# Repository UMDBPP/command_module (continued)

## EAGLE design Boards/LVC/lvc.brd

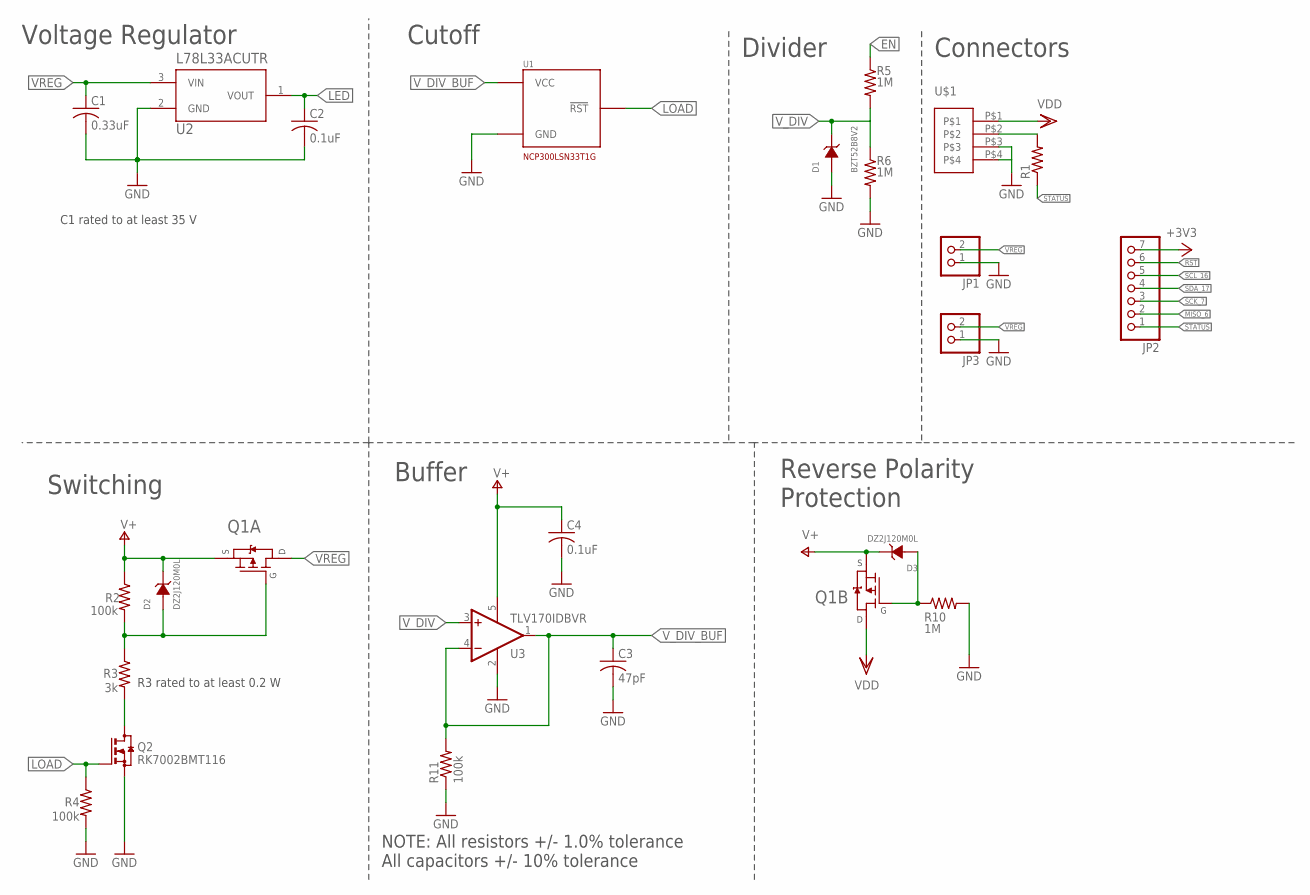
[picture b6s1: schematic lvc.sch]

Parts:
C1: 0.33uF; C0603
C2, C4: 0.1uF; C0603
C3: 47pF; C0603
D1: BZT52B8V2; SOD123
D2, D3: DZ2J120M0L; SMINI2-F5-B
JP1, JP3: PINHD-1X2; 1X02
JP2: PINHD-1X7; 1X07
Q1: SI7997DP; POWERPAK-SO-8-DUAL
Q2: RK7002BMT116; SOT23
R1: R-US_R0603; R0603
R2, R4, R11: 100k; R0603
R3: 3k; R0603
R5, R6, R10: 1M; R0603
U1: NCP300LSN33T1G; SOT23-5
U2: L78L33ACUTR; SOT-89
U3: TLV170IDBVR; SOT23-DBV
U$1: MICROCLASP_4; 4_PIN_MICROCLASP

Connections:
EN: R5.1
GND: C1.2, C2.2, C3.2, C4.2, D1.A, JP1.1, JP3.1, Q2.2 (S), R4.2, R6.2, R10.2, R11.1, U1.3 (GND), U2.2 (GND), U3.2 (V-), U$1.P$3, U$1.P$4
LED: C2.1, U2.1 (VOUT)
LOAD: Q2.1 (G), R4.1, U1.1 (!RST!)
MISO_6: JP2.2
unnamed: R1.2, U$1.P$2
unnamed: D2.A, Q1.4 (G), R2.2, R3.1
unnamed: D3.A, Q1.2 (G), R10.1
unnamed: Q2.3 (D), R3.2
RST: JP2.6
SCK_7: JP2.3
SCL_16: JP2.5
SDA_17: JP2.4
STATUS: JP2.1, R1.1
V+: C4.1, D2.C, D3.C, Q1.1 (S), Q1.3 (S), R2.1, U3.5 (V+)
VDD: Q1.7 (D), Q1.8 (D), Q1.8L (D), U$1.P$1
VREG: C1.1, JP1.2, JP3.2, Q1.5 (D), Q1.5L (D), Q1.6 (D), U2.3 (VIN)
V_DIV: D1.C, R5.2, R6.1, U3.3 (+IN)
V_DIV_BUF: C3.1, R11.2, U1.2 (VCC), U3.1 (OUT), U3.4 (-IN)

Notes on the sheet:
Voltage Regulator
Switching
Divider
Connectors
Reverse Polarity Protection
Cutoff
NOTE: All resistors +/- 1.0% tolerance All capacitors +/- 10% tolerance
C1 rated to at least 35 V
R3 rated to at least 0.2 W
Buffer

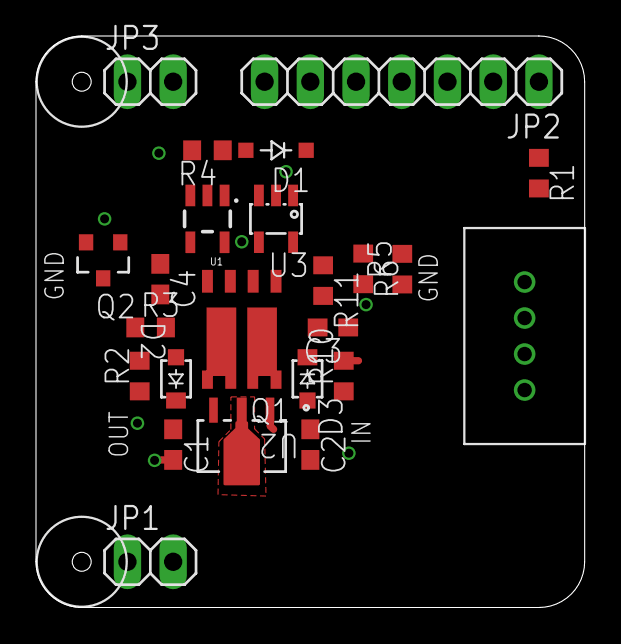
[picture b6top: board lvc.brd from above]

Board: 2 copper layers, 30.5 x 31.8 mm, 24 parts (0 on the bottom side), 13 nets.

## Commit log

2020-01-08 Initial commit with boards
2020-01-09 Routed cell tracker board with power reg
2020-01-18 Cell tracker V3 routed
2020-01-19 Cleaned up the BITS schematic
2020-01-19 cleaned up cell schematic
2020-01-20 Removing 3v3 line, fixing the MOSFET I broke
2020-01-20 Cell Mosfet swap
2020-01-20 General board parts placement for BITS
2020-01-21 Dump of CAD files
2020-01-21 reverted bits schematic back to my last commit"
2020-01-21 Revert "reverted bits schematic back to my last commit""
    This reverts commit d8380e26c9c134d67ee78542be9b2ca2b8e420f0.
2020-01-21 Better fidelity cad
2020-01-21 Add cmdLibs lib
2020-01-21 Maybe fixing supply 1
2020-01-21 v7 Compatible file upload
2020-01-21 Integrate the BITS XBee
2020-01-21 Pushing the compatible version
2020-01-21 Updated the inductor and mosfet in cell schematic
2020-01-21 Adding connector to lib
2020-01-22 routed bits board
2020-01-22 Created an alternate board
2020-01-22 bits board try 2
2020-01-23 put connector on cell board, plus lots of cad work
2020-01-24 a whole lot of finshed nonsense
2020-02-04 All of the changes with CAD and electronics since switching to the microclasp connectors
2020-02-05 fixes and design review slides
2020-02-16 Updated boards
2020-05-13 Reorganizing files for new boards
2020-05-13 Fixing Errors, ditching coincell
2020-05-16 Fixing BITS brd
2020-05-19 Bunches of CAD, but I don't like CAD
2020-05-29 Box Passthroughs, fixing Iridium Board
2020-06-15 not much
2020-06-15 Adding Gitignore for s#h and b#d
2020-06-15 Changing antenna conf
2020-06-15 Putting all the code into this repo
2020-06-15 modding GS for choppy
2020-06-19 updating resistors for correct cutoff
2020-06-26 Code+nearly completed boards
2020-07-03 Moved libs, adding isolator
2020-07-04 More stuff, close, not done
2020-07-05 Finishing touches for Cell3.2
2020-07-06 Finalizing BITS v3.2
2020-07-12 Final board export/cam, code libraries fld
2020-07-13 Handling R values
2020-07-14 minor R val changes, STEP generation
2020-07-26 API testing/cellv3.1trigger software failREP
2020-07-26 Added board step files to CAD fld
2020-07-27 more liteAPRS debugging
2020-07-29 BITS3v1 flight code, liteAPRS code
2020-08-01 CellCode
2020-08-02 jtXBee updates
2020-08-02 Include active jtXBee files
2020-08-03 celltracker sms_rx done, memredux
2020-08-07 NS92 prelim code FRZ
2020-08-17 Cell Assem Fin
2020-08-20 Cell Board appears to work
2020-08-26 New GPS procedures
2020-08-29 NewCell fixes
2020-08-30 Cell3.2 working, freeze
2020-08-30 NS93_code_FRZ
2020-09-03 Debugging Cell3v2
2020-09-15 buffer simplification
2020-10-09 New Testing File, v3.2 test
2020-10-16 New folder for test code, with in house gps lib
2020-10-16 setting up gps lib test
2021-01-09 Trying some new hardware configs
2021-01-11 changing some colors and taking screenshots
2021-01-15 a commit
2021-01-20 plate mounting bolt holes
2021-01-25 Adding a copy of the AdafruitRFM95 board for ref
2021-01-25 LightAPRS switching reg/LVC updates
2021-01-25 routed lightAPRS LVC
2021-01-26 Finished new LightAPRS LVC/REG
2021-02-01 Cutting down the adafruit rfm board
2021-02-20 box fixes
2021-03-14 Box changes
2021-03-15 New_lid
2021-03-18 Adding in Bitsv2 board CAD
2021-03-18 re-order/confirm LVC fix
2021-03-31 Plate mounting holes
2021-04-03 new_reg work
    LMR50410XF reg design to cover and possibly replace LMR16020 for <1A command things
2021-07-06 plate for v2 bits brd
2021-07-08 lightAPRS code fix
2021-08-08 re-arrange some file structure, init boxv4
2021-08-08 Box v4 draft
2021-08-19 New reg board
    LM20242
2021-09-16 routed board...?
2021-09-26 improved spacing between rockblock and bits board on plate
2021-10-03 BITSv4
    omg I need a clock so bad
2021-10-04 LED reposition
2021-10-09 connector move
2021-10-13 TextMove
2021-12-11 new choppy
2022-01-02 code for second xbee trigger using arduino pro mini
2022-01-12 file changes
2022-04-16 TestedBoard
    omg_it_works
2022-04-17 BoardUpdate
2022-04-19 Clone v3.2 to v4
2022-04-19 Comments, lots of Comments
2022-04-21 Completed Commenting Primary File
2022-04-21 Enough changes a test should happen
2022-04-21 Added voltage reporting
2022-04-22 Unbroke the code again
2022-04-22 AvgAscentRate added
2022-04-25 FixingErrors
    snprintf unhappy, modifying that
2022-04-25 Another Fix
2023-05-26 new ghoul xbee
2023-07-31 bits v5 board begins
2023-07-31 BITSv5 updates
2023-08-11 BITSv5 sch almost done
2023-08-13 more bits updates
2023-08-18 bits v5 board nearly done
2023-08-19 several hundred bits v5 errors later
2023-08-20 bits v5 board feedback added
2023-08-20 no more 5 am commits
2023-08-23 BITSv5 layout changes
2023-08-25 small update to BITSv5 for review
2023-08-26 BITSv5 board done
2023-08-26 xbee joint board begins
2023-08-28 xbee joint board updates
2023-08-30 xbee joint and bits updates
2023-09-04 most up to date bits and xbee joint
2023-09-04 added button to BITS5
2023-09-04 working on xbee joint
2023-09-05 xbee joint layout almost complete
2023-09-05 BITSv5 USB change
2023-09-05 BITSv5 added additional Xbee connector
2023-10-09 ns122 updates to do
2023-10-19 bits v5 w/ dorji radio
2023-10-19 dorji joint?
2023-10-23 ordered new joint and bits
2023-11-03 added kicad-lib submodule
2023-11-05 messing with RP2040 code
2023-11-05 more testing code
2023-11-05 submodule stuff
2023-11-05 submodule fixes
2023-11-05 more submodule fixes
2023-11-05 starting to refactor radio library
2023-11-06 added blink to BITSv5 test code
2023-11-06 additional reference code
2023-11-07 more BITSv5 code experimentation
2023-11-08 radio test code that compiles?
2023-11-08 trying serial input too
2023-11-09 xbee joint test code
2023-11-09 last ugh?
2023-11-10 xbee joint radio test code
2023-11-10 this radio is annoying me
2023-11-10 tx continuous wave works
2023-11-10 xbee joint +25 dBm continuous wave
2023-11-10 more radio code
2023-11-10 receive IRQ works now
2023-11-11 transmit and receive on BITS and (Not)Xbee Joint, packets are recognized (valid preamble detected) but a header error is thrown on receive (LoRa header CRC error)
2023-11-14 more xbee joint code
2023-11-14 yeppers
2023-11-16 minor (Not)Xbee Joint refactor, deleted LittleFS from (Not)Xbee Joint too
2023-11-27 README typo that was there for god knows how long
2023-11-28 minor (not)xbee joint code change
2023-11-29 more (not)xbee joint futzing, still doesn't work :(
2023-12-08 cleaned up some radio code
2023-12-09 the radios were working like an hour ago
2023-12-09 RADIO WORKS
2023-12-09 saved some radio test proof and code
2023-12-09 more clean up
2023-12-10 started big sx1262 lib refactor
2023-12-10 init SX1262 lib and hopefully fix crusty submodule issue
2023-12-10 using sx1262 lib in BITSv5 now, also more submodule decrustification
2023-12-10 added multiple build targets for BITSv5
2023-12-10 (Not)Xbee Joint automation
2023-12-11 (not)xbee joint <-> bits lora comms work, just not ping pong for some reason
2023-12-11 automation fixes
2023-12-11 automation fixes again
2023-12-11 deleted kicad-lib submodule
2023-12-11 re-added kicad-lib submodule tracking main
2023-12-11 trying to fix these submodules
2023-12-11 these submodules omg
2023-12-11 geez
2023-12-11 BITSv5 software README
2023-12-16 updated release tags for BITSv5 and (Not)Xbee Joint to v0.0.1
2023-12-22 first pass at MS5607 library
2023-12-22 created MS5607 library submodule
2023-12-22 ok now BITSv5 compiles with MS5607 lib
2024-01-18 added some new libraries (rp2040-config, rp2040-console, std-cmd)
2024-01-24 started adding rp2040-console support to (Not)Xbee Joint test code
2024-01-26 adding console support to (Not)Xbee Joint test code
2024-01-26 I think console/radio test code ready
2024-01-26 compiles with config library
2024-01-26 send and lstn commands work
2024-01-27 moved BITS header and created BITS gps-test
2024-01-27 updated rp2040 config and console
2024-01-27 clean up changes
2024-01-27 changed BITsv5 Test auto build to only trigger on pushes to BITSv5 test code
2024-01-27 testing new BITSv5 auto build
2024-01-31 starting BITSv5.1 hardware rev
2024-01-31 changed BITSv5 antennas to ufl, added TIMEPULSE and EXTINT GPIOs, and exposed GPIO UART over header
2024-02-01 BITSv5.1 ready for review
2024-02-01 nvm I want BITSv5 to have a chip antenna
2024-02-01 finished GPS chip antenna, removed SOICbite for test points because couldn't find space
2024-02-01 clean up
2024-02-02 BITSv5.1 ready for order, Gerbers generated
2024-02-02 new art footprints
2024-02-02 updated rp2040-console
2024-02-04 BITSv5.1 STEP file and dimensions
2024-02-08 added logs from v5 GPS lock attempts
2024-02-11 BITS radio no long draws almost 100 mA idle
2024-02-11 updated drf1262 lib
2024-02-11 syncing BITSv5 and (Not)Xbee Joint boards
2024-02-13 added interrupt support to DRF1262 lib and (Not)Xbee Joint code
2024-02-13 sync drf1262 lib
2024-02-14 refined the interrupt implementation for the drf1262 library, there are rough edges but it's fine
2024-02-14 tried to see if new txen fix for the radio would make the GPS magically work but it didn't :(
2024-02-14 synced drf1262 library
2024-02-17 starting power changes for BITSv5.2
2024-02-18 BITSv5.2 new power system laid out
2024-02-19 ordered BITSv5.2
2024-02-25 changes for ns-124
2024-02-25 potentially flyable ns-124 changes
2024-03-02 ns124 aftermath changes
2024-03-02 BITSv5.2 changes
2024-03-02 libraries updates
2024-03-02 rp2040 libraries sync
2024-03-02 fixed FRAM library include for (Not)Xbee Joint
2024-03-03 fixed Models:Drawings
2024-03-06 BITS improvements, logging test and radio irq
2024-03-06 (Not)Xbee Joint updates
2024-03-07 FRAM logging in progress, addressing hopefully finally works properly now
2024-03-07 logging and dumping from FRAM working
2024-03-08 BITS changes
2024-03-09 radio-test code for BITSv5.2 works now, RX and TX
2024-03-10 BITS radio working again
2024-03-13 Copied over some structs from libnmea and outlined how parsing could operate
2024-03-13 Added a little more to parsing
2024-03-13 Copied several more functions
2024-03-15 Finished first draft
2024-03-15 radio test updates
2024-03-22 updates for NS-125, very hasty/messy changes
2024-03-22 first pass at iridium driver for BITSv5
2024-03-22 update libraries
2024-03-22 minor changes
2024-03-26 iridium driver updates, SBDIX parsing broken but basics confirmed working
2024-04-19 new header files for config and code sharing
2024-04-19 made Not_XbeeJoint autobuild only run on relevant changes
2024-07-19 actually going to try writing the actual fligh code now
2025-02-14 saving state before minimizing this test project
2025-02-24 minimal GPS example code, need to test
2025-02-24 minimal radio example code, need to test
2025-02-24 iridium test code, need to test, not full minimal example yet
2025-02-27 tested basic functionality, def some issues to work out, also added channel activity detection which needs to be tested
2025-04-09 first attempts at BITSv5 arduino code because it's time I got my shit together, also featuring modified arduino-cli docker container for building
2025-04-09 trying to commit docker container source
2025-04-11 refactor in progress
2025-04-21 minor GPS parsing change for BITSv4, TinyGPS -> TinyGPSPlus
2025-11-21 new build with new GHOUL Xbee Address 0x4256DDBC
2025-11-21 updated Xbee address
2025-11-21 BITSv4 reproducible build support with arduino-cli
2025-11-22 maybe actually real GPS parse updates this time? I really don't know what happened and I'm going a little crazy lowkey
2025-11-26 actual GPS parse update
2025-11-27 update gitignore to ignore files in build directories
2025-11-27 update gitignore to ignore all DS_Store
2025-11-27 remove DS_Store
2025-11-27 add github action to build BITSv4 code
2025-11-27 update action to apply to branch
2025-11-27 update action so I can test it with PR
2025-11-27 change arduino-cli install directory bc idk what I'm doing
2025-11-27 update action
2025-11-27 added docs on auto build system
2025-11-27 Create BITSv4 Build System (#24)
    * BITSv4 reproducible build support with arduino-cli
    * update gitignore to ignore files in build directories
    * update gitignore to ignore all DS_Store
    * remove DS_Store
    * add github action to build BITSv4 code
    * update action to apply to branch
